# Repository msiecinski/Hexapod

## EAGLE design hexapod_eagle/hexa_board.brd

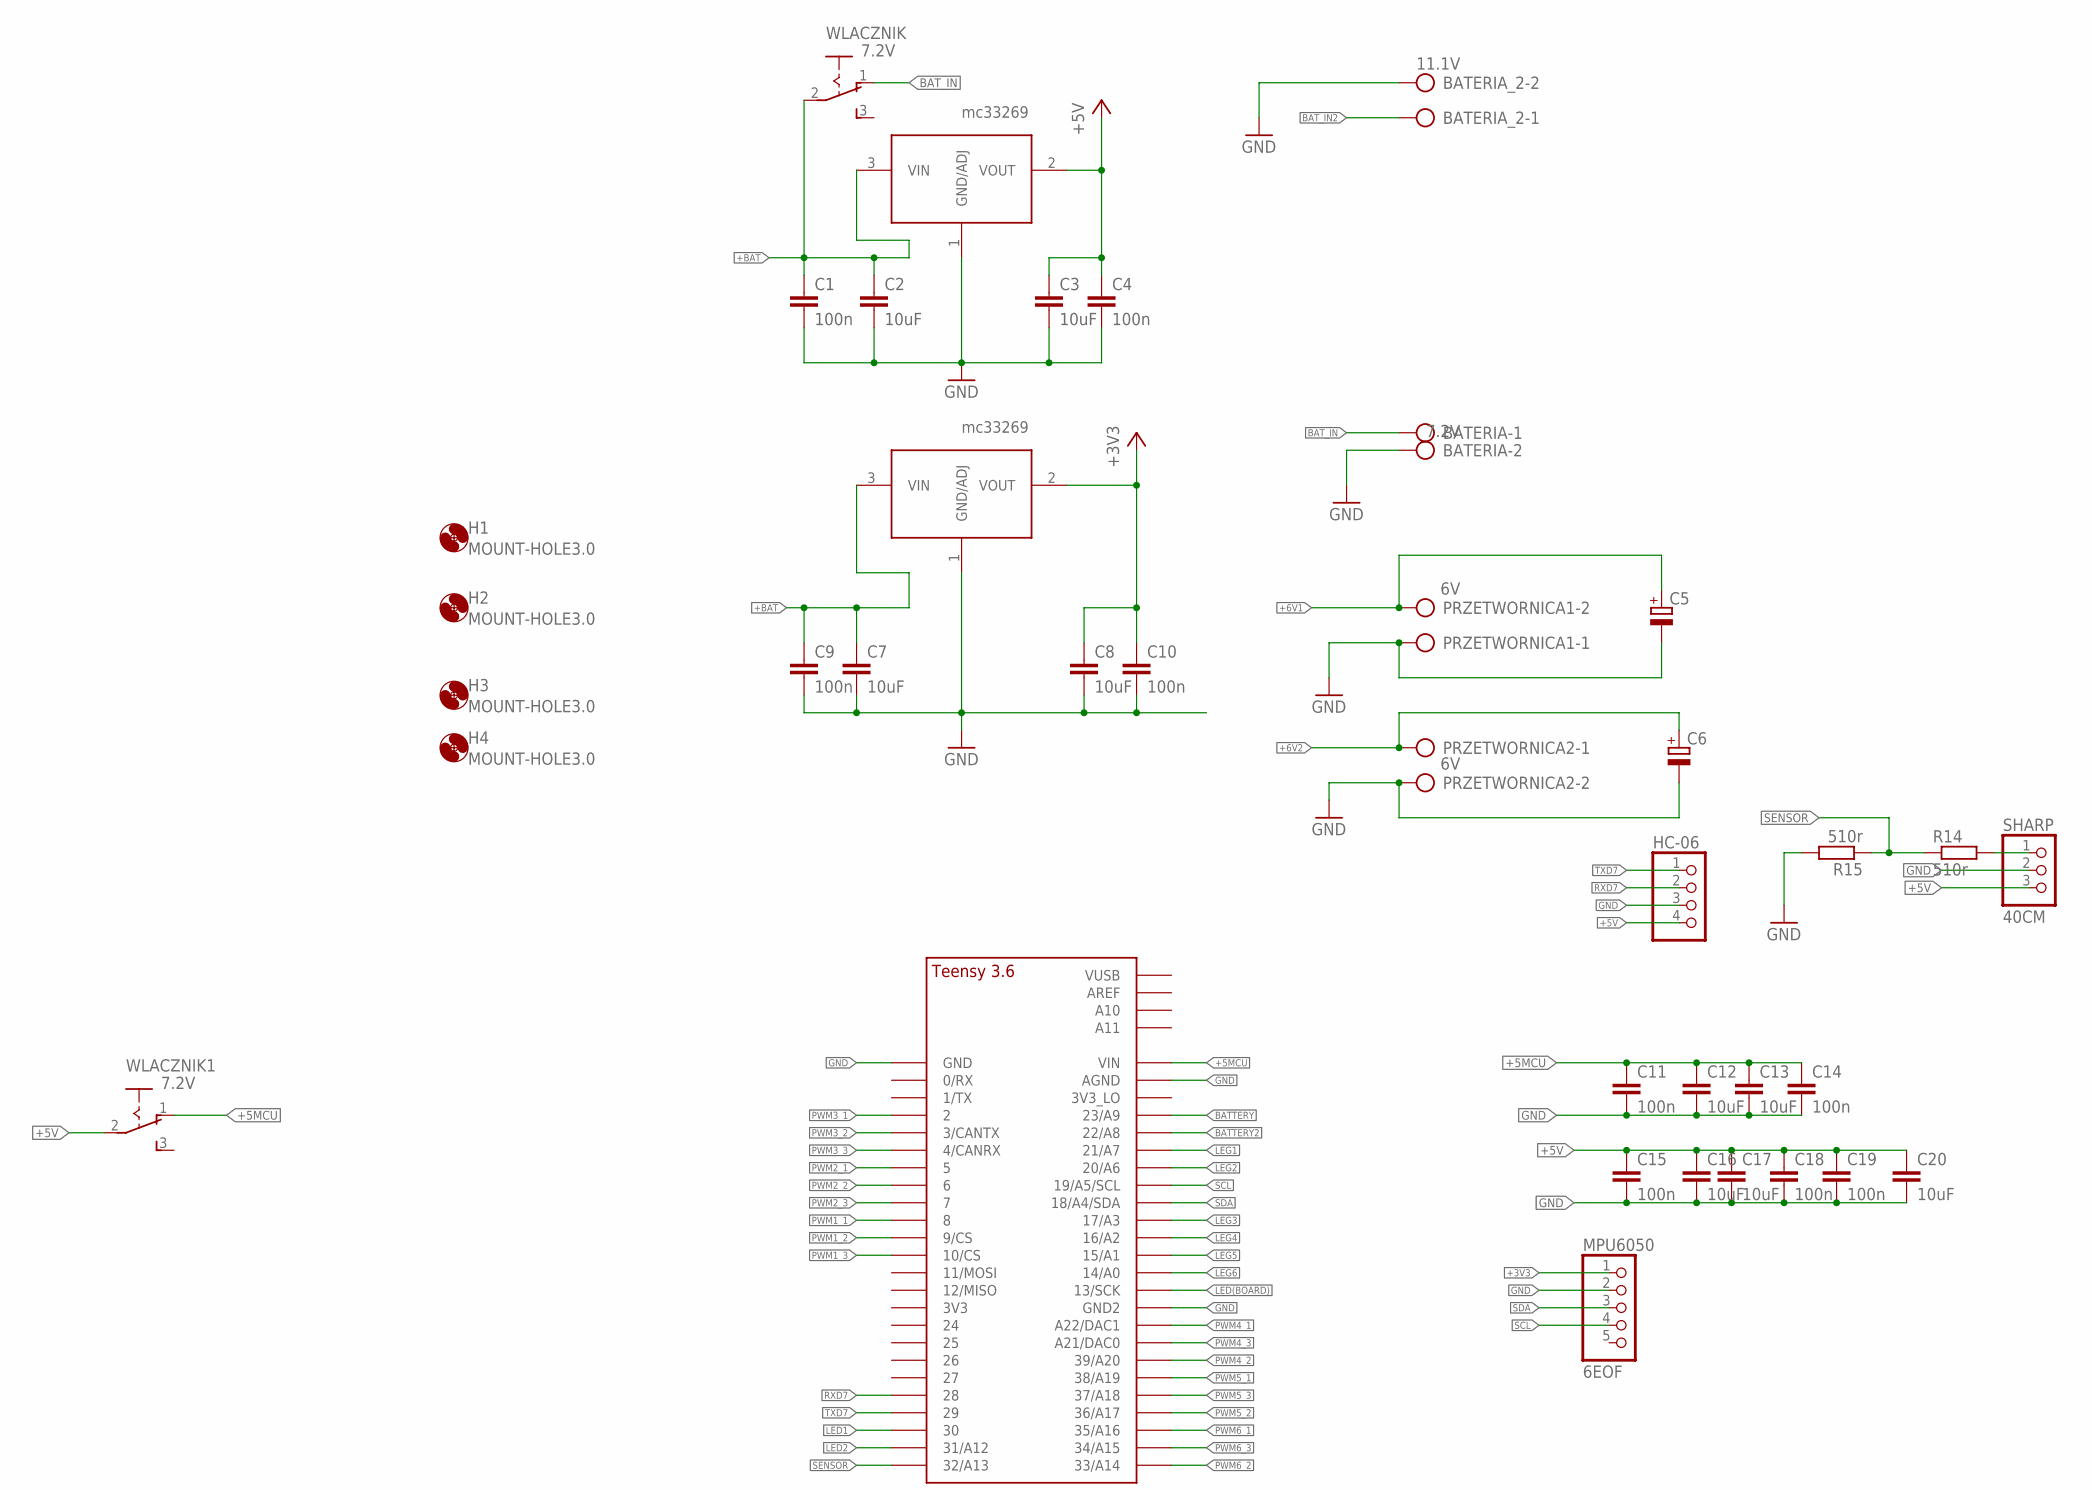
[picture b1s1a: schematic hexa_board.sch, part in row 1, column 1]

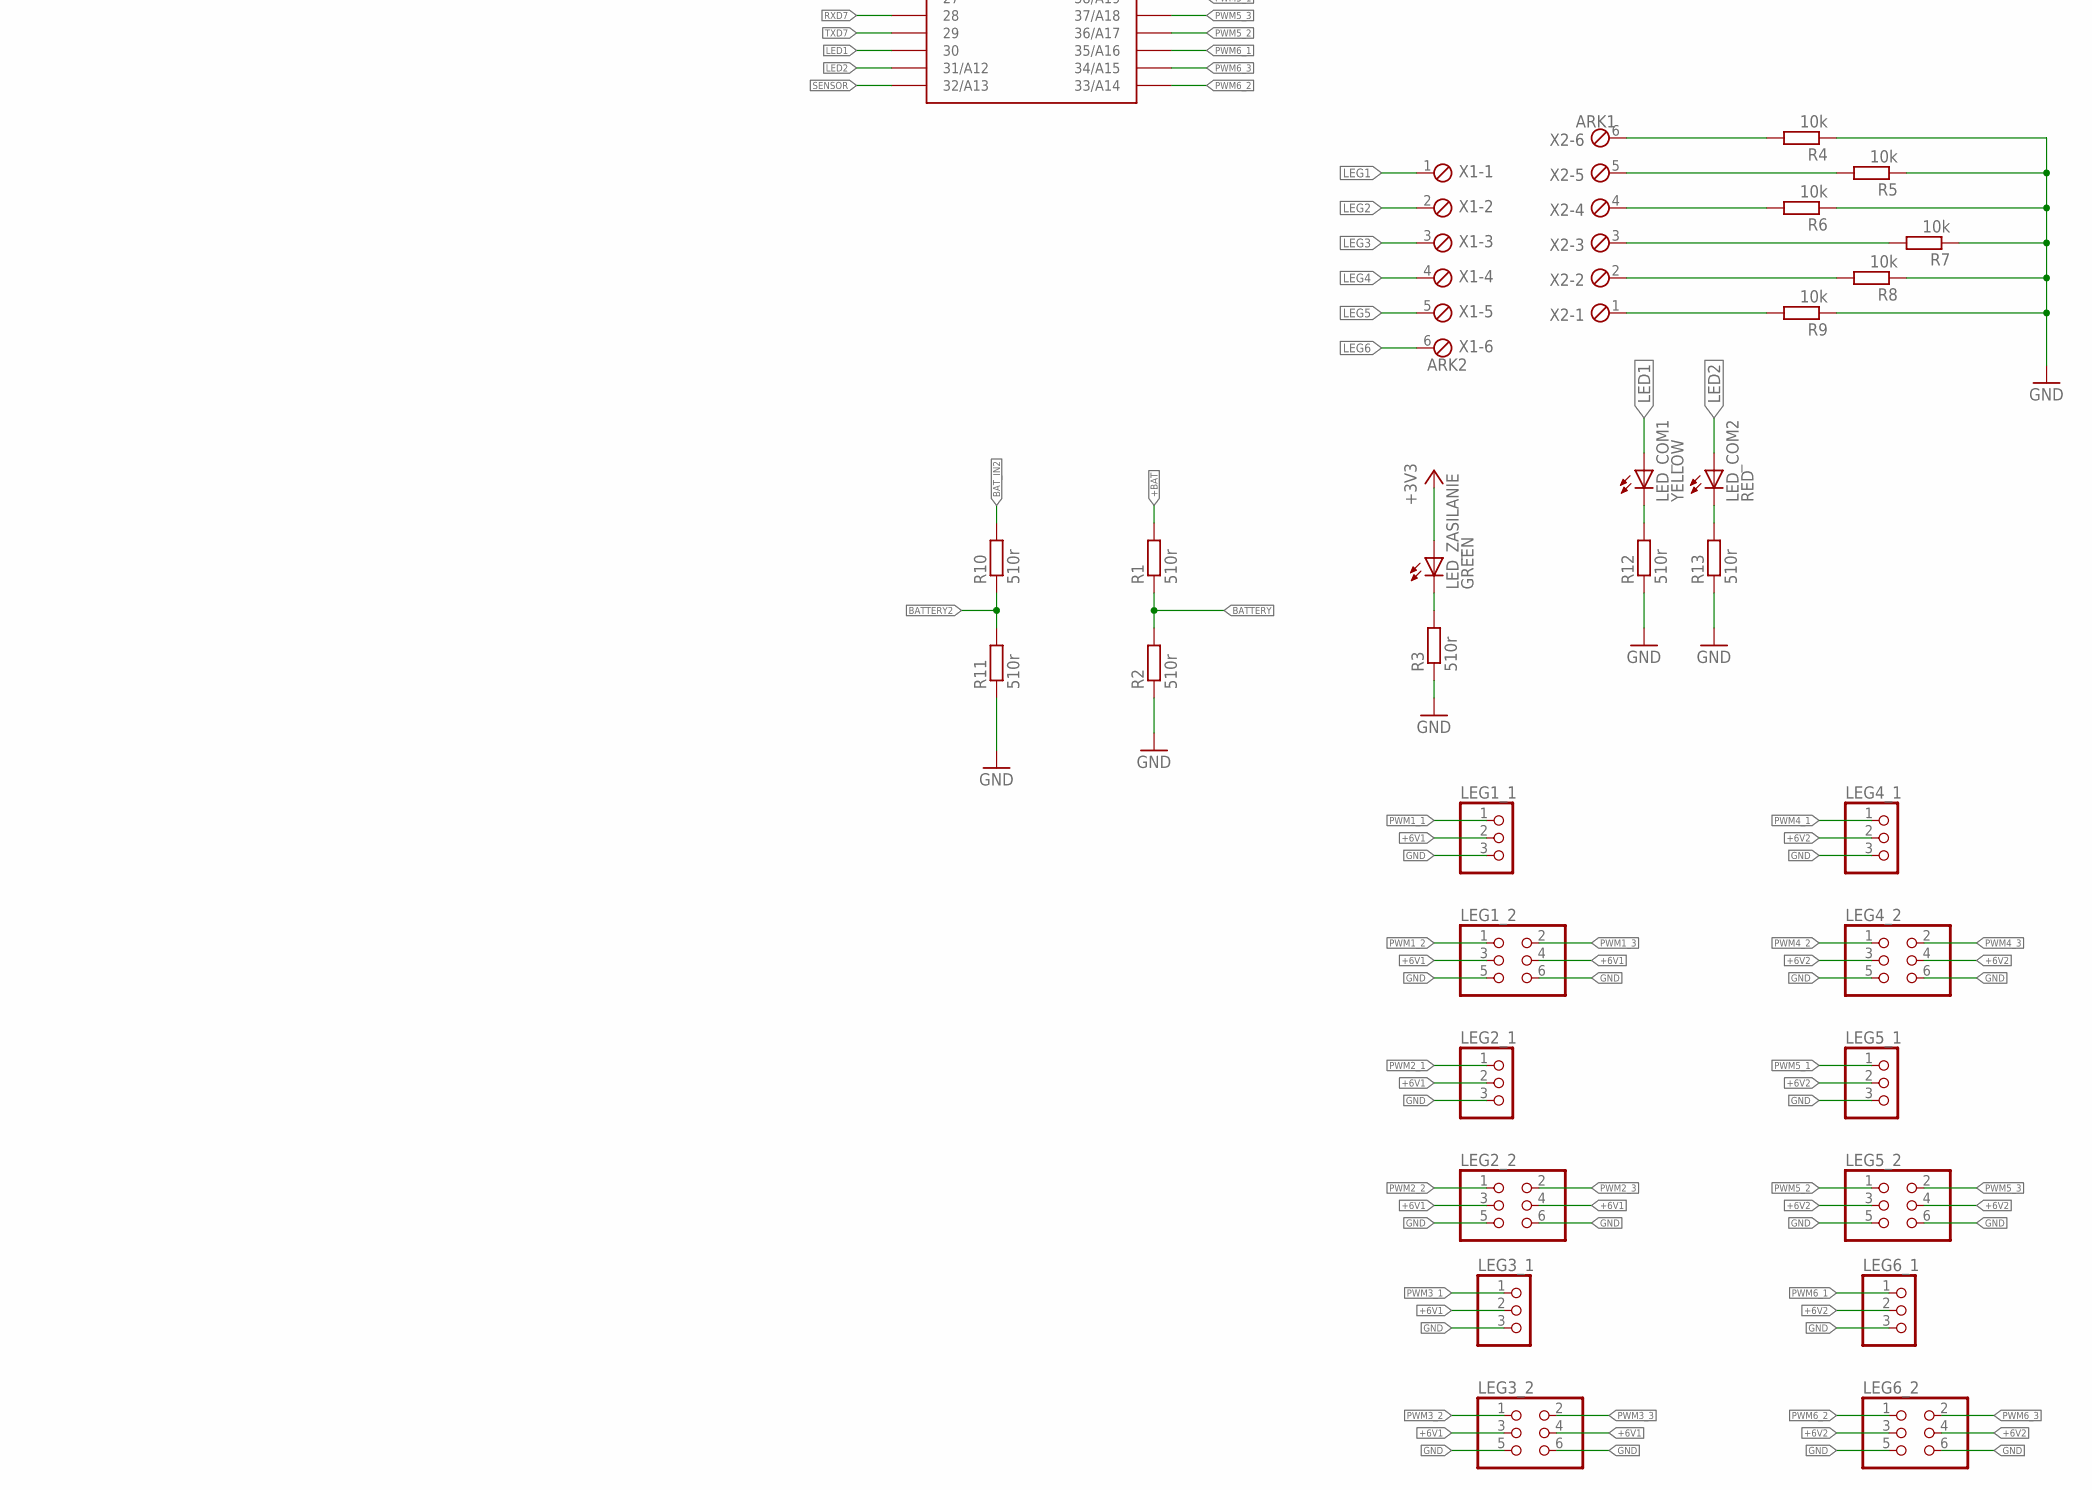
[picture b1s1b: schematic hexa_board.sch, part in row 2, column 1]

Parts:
3V, 5V: MC33269; TO220
BATERIA: 7.2V; AK300/2
BATERIA_2: 11.1V; AK300/2
C1, C4, C9, C10, C11, C14, C15, C18, C19: 100n; C0805
C2, C3, C7, C8, C12, C13, C16, C17, C20: 10uF; C1206
C5, C6: CPOL-EU150CLZ-1014; 150CLZ-1014
H1, H2, H3, H4: MOUNT-HOLE3.0; 3,0
HC-06: PINHD-1X4; 1X04
LED_COM1: YELLOW; SML0805
LED_COM2: RED; SML0805
LED_ZASILANIE: GREEN; SML0805
LEG1_1, LEG2_1, LEG3_1, LEG4_1, LEG5_1, LEG6_1: PINHD-1X3; 1X03
LEG1_2, LEG2_2, LEG3_2, LEG4_2, LEG5_2, LEG6_2: PINHD-2X3; 2X03
MPU6050: 6EOF; 1X05
PRZETWORNICA1, PRZETWORNICA2: 6V; AK300/2
R1, R2, R3, R10, R11, R12, R13, R14, R15: 510r; R0805
R4, R5, R6, R7, R8, R9: 10k; R0805
SHARP: 40CM; 1X03
TEENSY41: TEENSY_3.5/3.6_BASIC
WLACZNIK, WLACZNIK1: 7.2V; 255SB
X1: ARK2; 6POL254
X2: ARK1; 6POL254

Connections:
+3V3: 3V.2 (VOUT), C8.1, C10.1, LED_ZASILANIE.A, MPU6050.1
+5MCU: C11.1, C12.1, C13.1, C14.1, TEENSY41.VIN, WLACZNIK1.1 (O)
+5V: 5V.2 (VOUT), C3.1, C4.1, C15.1, C16.1, C17.1, C18.1, C19.1, C20.1, HC-06.4, SHARP.3, WLACZNIK1.2
+6V1: C5.+, LEG1_1.2, LEG1_2.3, LEG1_2.4, LEG2_1.2, LEG2_2.3, LEG2_2.4, LEG3_1.2, LEG3_2.3, LEG3_2.4, PRZETWORNICA1.2
+6V2: C6.+, LEG4_1.2, LEG4_2.3, LEG4_2.4, LEG5_1.2, LEG5_2.3, LEG5_2.4, LEG6_1.2, LEG6_2.3, LEG6_2.4, PRZETWORNICA2.1
+BAT: 3V.3 (VIN), 5V.3 (VIN), C1.1, C2.1, C7.1, C9.1, R1.2, WLACZNIK.2
BATTERY: R1.1, R2.2, TEENSY41.23/A9
BATTERY2: R10.1, R11.2, TEENSY41.22/A8
BAT_IN: BATERIA.1, WLACZNIK.1 (O)
BAT_IN2: BATERIA_2.1, R10.2
GND: 3V.1 (GND/ADJ), 5V.1 (GND/ADJ), BATERIA.2, BATERIA_2.2, C1.2, C2.2, C3.2, C4.2, C5.-, C6.-, C7.2, C8.2, C9.2, C10.2, C11.2, C12.2, C13.2, C14.2, C15.2, C16.2, C17.2, C18.2, C19.2, C20.2, HC-06.3, LEG1_1.3, LEG1_2.5, LEG1_2.6, LEG2_1.3, LEG2_2.5, LEG2_2.6, LEG3_1.3, LEG3_2.5, LEG3_2.6, LEG4_1.3, LEG4_2.5, LEG4_2.6, LEG5_1.3, LEG5_2.5, LEG5_2.6, LEG6_1.3, LEG6_2.5, LEG6_2.6, MPU6050.2, PRZETWORNICA1.1, PRZETWORNICA2.2, R2.1, R3.1, R4.1, R5.1, R6.1, R7.1, R8.1, R9.1, R11.1, R12.1, R13.1, R15.2, SHARP.2, TEENSY41.AGND, TEENSY41.GND, TEENSY41.GND2
LED1: LED_COM1.A, TEENSY41.30
LED2: LED_COM2.A, TEENSY41.31/A12
LED(BOARD): TEENSY41.13/SCK
LEG1: TEENSY41.21/A7, X1.1
LEG2: TEENSY41.20/A6, X1.2
LEG3: TEENSY41.17/A3, X1.3
LEG4: TEENSY41.16/A2, X1.4
LEG5: TEENSY41.15/A1, X1.5
LEG6: TEENSY41.14/A0, X1.6
unnamed: R4.2, X2.6
unnamed: R5.2, X2.5
unnamed: R6.2, X2.4
unnamed: LED_ZASILANIE.C, R3.2
unnamed: R7.2, X2.3
unnamed: R8.2, X2.2
unnamed: R9.2, X2.1
unnamed: LED_COM1.C, R12.2
unnamed: LED_COM2.C, R13.2
unnamed: R14.2, SHARP.1
PWM1_1: LEG1_1.1, TEENSY41.8
PWM1_2: LEG1_2.1, TEENSY41.9/CS
PWM1_3: LEG1_2.2, TEENSY41.10/CS
PWM2_1: LEG2_1.1, TEENSY41.5
PWM2_2: LEG2_2.1, TEENSY41.6
PWM2_3: LEG2_2.2, TEENSY41.7
PWM3_1: LEG3_1.1, TEENSY41.2
PWM3_2: LEG3_2.1, TEENSY41.3/CANTX
PWM3_3: LEG3_2.2, TEENSY41.4/CANRX
PWM4_1: LEG4_1.1, TEENSY41.A22/DAC1
PWM4_2: LEG4_2.1, TEENSY41.39/A20
PWM4_3: LEG4_2.2, TEENSY41.21/DAC0 (A21/DAC0)
PWM5_1: LEG5_1.1, TEENSY41.38/A19
PWM5_2: LEG5_2.1, TEENSY41.36/A17
PWM5_3: LEG5_2.2, TEENSY41.37/A18
PWM6_1: LEG6_1.1, TEENSY41.35/A16
PWM6_2: LEG6_2.1, TEENSY41.33/A14
PWM6_3: LEG6_2.2, TEENSY41.34/A15
RXD7: HC-06.2, TEENSY41.28
SCL: MPU6050.4, TEENSY41.19/A5/SCL
SDA: MPU6050.3, TEENSY41.18/A4/SDA
SENSOR: R14.1, R15.1, TEENSY41.32/A13
TXD7: HC-06.1, TEENSY41.29

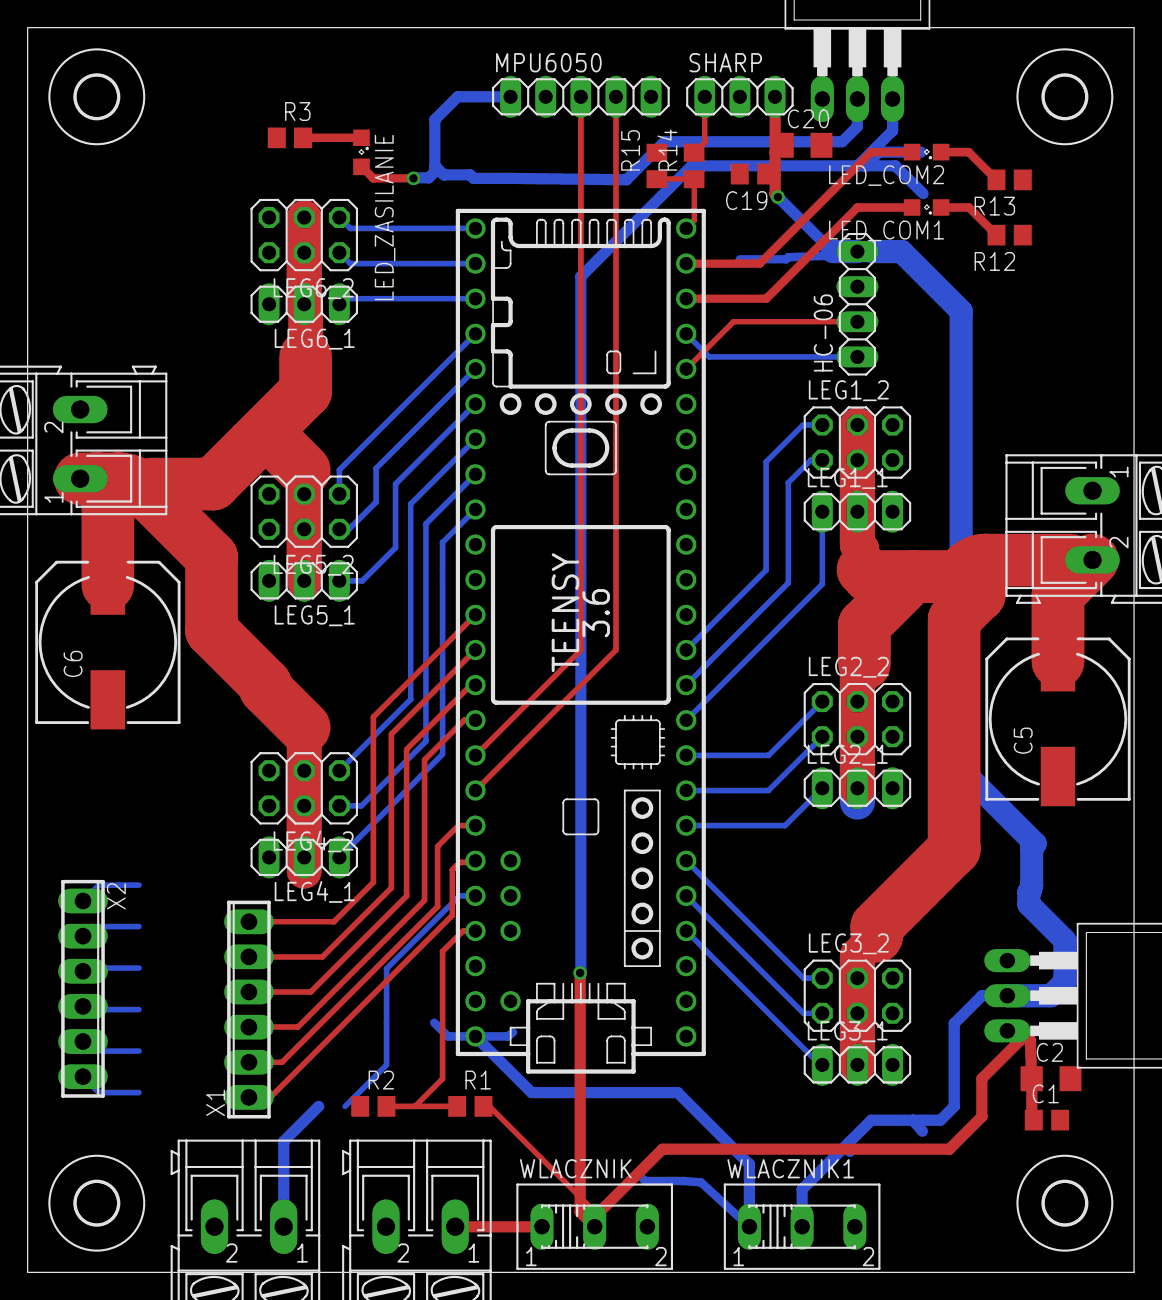
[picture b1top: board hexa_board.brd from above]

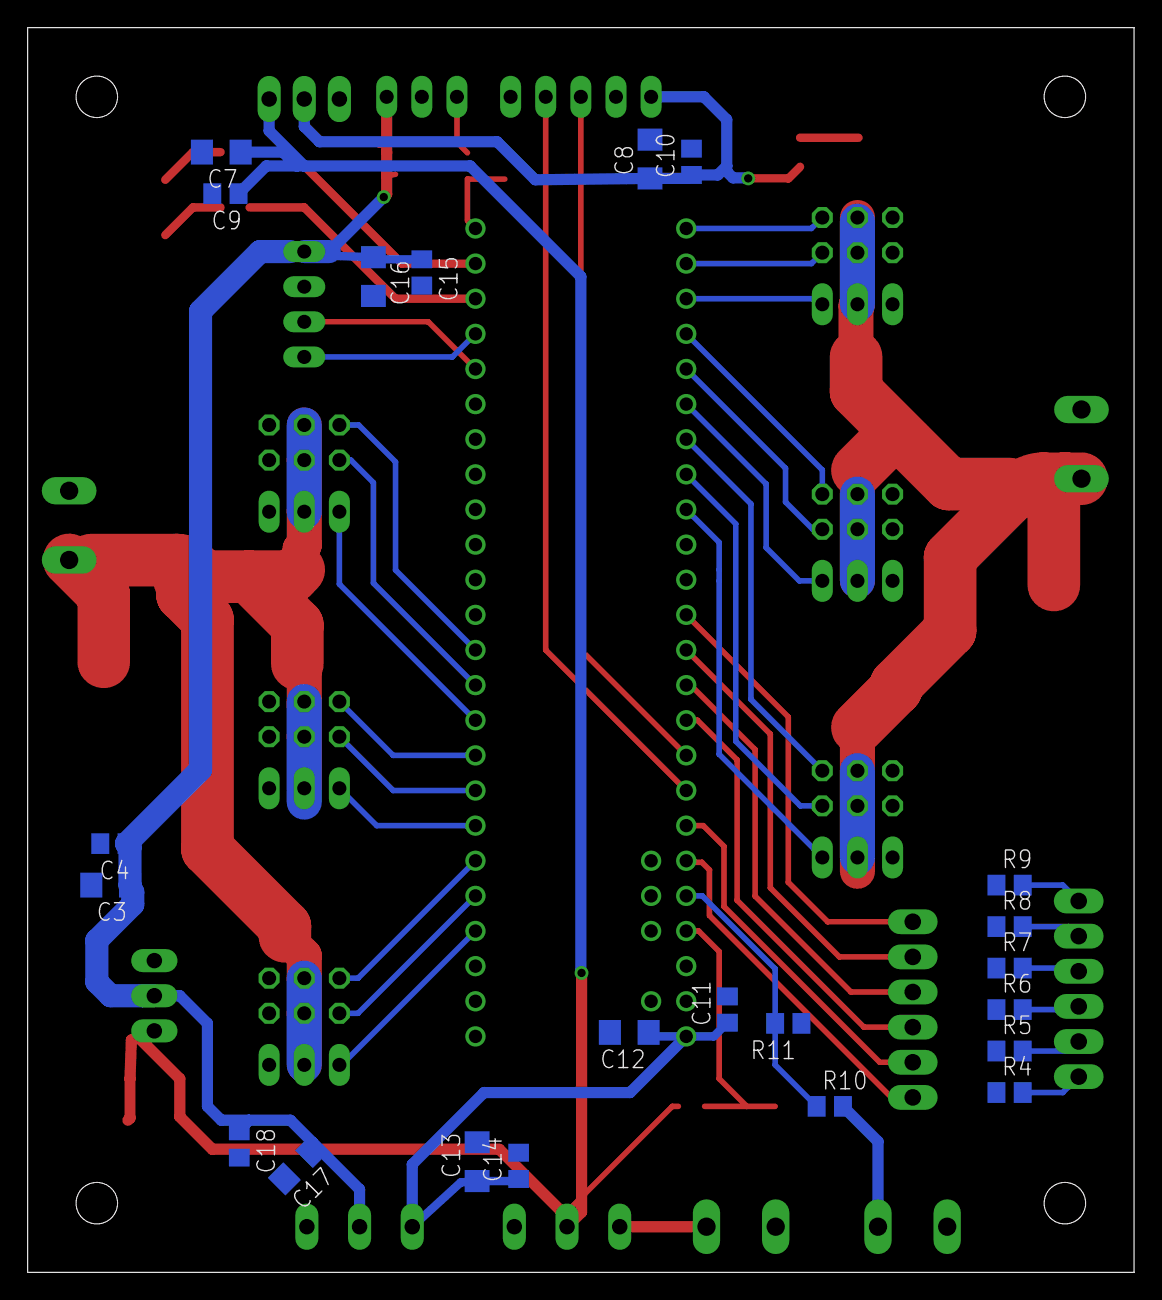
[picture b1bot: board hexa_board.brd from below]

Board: 2 copper layers, 80.0 x 90.0 mm, 68 parts (22 on the bottom side), 52 nets.

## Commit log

2020-10-04 Hexapod eagle files
    Hexapod main board eagle files v1
2020-10-04 Solidwors project files
    Hexapod mechanics construction files in solidworks
2020-10-04 Hexapod source code
    Hexapod source code
    IDE: Visual studio code with platformio extension
2020-10-04 Hexapod board v2
    Changelog:
    -new package for voltage regulator
    -supply for ground sensor
    -fix voltage sensor
    -second battery voltage sensor
2020-10-04 Board v2
    Changelog:
    -on/off swich for power mcu(was in last update)
    -add 2 leds for comunication
    -some positions changes
2020-10-13 Fixed SetPosition function
    Added copy delay flag
2020-10-13 SlideHorizontal function upadate
    Fix errors in SlideHorizontal function, now probably is working well.
2020-10-14 Update SetupLeg
    Added init for all 18 joints.
2020-10-17 Update delay
    Added scaling to the delay
2020-10-17 Update pwm function
    Some changes in pwm genereting function.
2020-10-17 Startup fix
    Fix startup for set position all legs.
2020-10-18 Clean DelayFunc function
    Clean DelayFunc function from blink led(was for interrupt test)
2020-10-18 Updates types and consts
2020-10-18 Updated PWM function
    Change variable type
2020-10-18 AngleToDuty update
    Added conditions if angle <0 or >180 degrees
2020-10-19 Some changes in moves functions
    -added SetAllLegs function
    -new version Move function
2020-10-19 Update .gitignore
    -added *.SLDPRT files
2020-10-19 Update .gitignore
    -added *.SLDASM files
2020-10-19 Added stl file
    -added 3d object(leg a2)
2020-10-19 Update kinemetics.cpp
    Some changes in InversKinematics function
2020-10-19 Update header
    -added SetAllLegs function to the header
2020-10-19 Update kinematics.cpp
    Change "0" postion angle q3 and some cosmetics changes.
2020-10-21 Update .gitignore
    Revers changes with *.SLDPRT files
2020-10-21 Update defines
    -added few defines
    -modify enum movetype
    -some minor changes
2020-10-21 Update movement
    Added new "API" function for control robot movement
2020-10-21 Add sldprt file
    Added missing sldprt file with part of leg.
2020-10-21 Added new files
    Fitrst implementation funtions used for connect with dualshock 4 and used it to control robot movement.
2020-10-21 Update movement.cpp
    update test function and some minor changes
2020-10-21 Update main.cpp
    New global variables added
    added calling SetupPS4 function(for usb init)
2020-10-21 Update main.cpp
    Fix setup startup postion all legs after reset
2020-10-21 minor changes
    Some minor changes
2020-10-23 Added leg A3 files
    First version parf of leg(A3)
2020-10-23 Change name
    Change name part of the leg
2020-10-28 Update board project
    -fix voltage regulator output
    -added tantalum capacitors (B size)instead cpol
2020-10-28 Update eagle board
    -added sharp sensor
    -some minor changes
2020-10-28 Sharrp sensor bard
    Added board for Sharp GP2Y0D340K sensor.
2020-10-29 Update Global_defines.hpp
    -new value for A2
    -new field for offsets in hexapod struct
    -some minor changes
2020-10-30 Update gyroscope.cpp
    Delete prints for debug and some minor changes.
2020-10-31 Uddate cad files
    Changes in hehapod "base":
    -added place for battery
    -added place for usb hub
    -added hole for usb cable(for programming teensy)
    -some minor changes
2020-10-31 Update hexa_board.brd
    Delete drill size error
2020-10-31 Update leg A3
    New wersion of leg part - A3
2020-11-07 Update movement.cpp
    Fix SetPosiotion function
2020-11-08 Update leg3
    New version of leg3, added place for limit switch
2020-11-09 Added new funtion in kinematics.cpp
    Added new function(RotateCordinat) for rotate cordinates(base on robot build)
2020-11-09 Fixes movenet functions problems
    -fix Move and SlideHorizontal problems
    -change some const value
2020-11-09 Update init.cpp
    Minor change
2020-11-09 Update control funtion
    Change in controll funtion, switch from ps4control.cpp to movement.cpp file
2020-11-09 Update leg A3
    -some changes in part of leg(A3)
2020-11-10 Update kinematics files
    Added support for second parameter(y) in funnction RotateCordinate.
2020-11-10 Support offset field
    Added first version of support to offset field in hexapod struct.
2020-11-11 Update movement
    Some upgrades in Move function, first test interation support for CheckGround funtion.
2020-11-11 Update CheckGround function
    -added function using to init "ground sensor pins"
    -added digital read from sensor pins in function GroundCheck
2020-11-11 Update movement.cpp
    CheckGround function update(almost ready)
2020-11-11 Update movement.cpp
    -ON function CheckGround
    -fixes bugs with using function CheckGround.
2020-11-11 Update LEG_A3.SLDPRT
    Probably final version of A3(leg part).
2020-11-11 minor changes
    -added some "optimalization", minor changes
2020-11-14 Update eagle files
    -change to ark leg sensor pins
    -change isolte value
    -esp32 cam-insted bluetooth/"wifi"
    -some minor changes
2020-11-22 Changes in cad files
    Build v2 for top part hexapod main board.
2021-02-25 Update
    Update move and kinematics functions
2021-02-25 Update
    Some updates
2021-02-25 Update movement.cpp
    Delete not necessary function
2021-03-02 kimenatics files update
    Minor changes
2021-03-02 Update for UART
    Some changes for init UART(for hc-06 module)
2021-03-03 Update movement.cpp
    Turn off quantization of move(offset)
2021-03-22 Update eagle schematic and board
    -added capacitors
    -added voltage divider
    -change package some capacitors
    -added on/off swich for power mcu
2021-03-22 Update eagle files
    -change positions some capacitors
    -change TXD/RXD lines
    -minor changes
2021-03-22 Update eagle files
    Change some capacitors package.
2021-03-23 Update cad files naming
    Change names cad files
2021-03-24 Update cad files
    Names update and some minor changes.
2021-03-24 Update cad files
    New names and minor changes.
2021-03-24 Update cad files
    Minor dimetions changes.
2021-03-24 Added assembling files
    Hexapod assembling cad files.
2021-03-24 Update .gitignore
    gitignore fix
2021-03-24 Update movement.cpp
    Minor changes
2021-03-29 Added new parts
    -added 2 new parts
    -update assembly
2021-03-29 Update cad files
    Minor changes
2021-03-30 Update cad files
    -some minor changes in "hats"
2021-03-31 Delete Kalman.hpp
    Delete not nessesery file
2021-03-31 Update Global_defines.hpp
    Minor change
2021-04-12 update kinematics files
    Added new function for calculate height offset to obtain set angle.
2021-04-12 Added bufor for calculate duty
    Added bufor for calculate duty, new flag(update) and changes delay setups.
2021-09-30 back to quantization of moves
    Turn back qantization of moves;
    miror changes;
2022-04-01 Update main.cpp
    test changes
